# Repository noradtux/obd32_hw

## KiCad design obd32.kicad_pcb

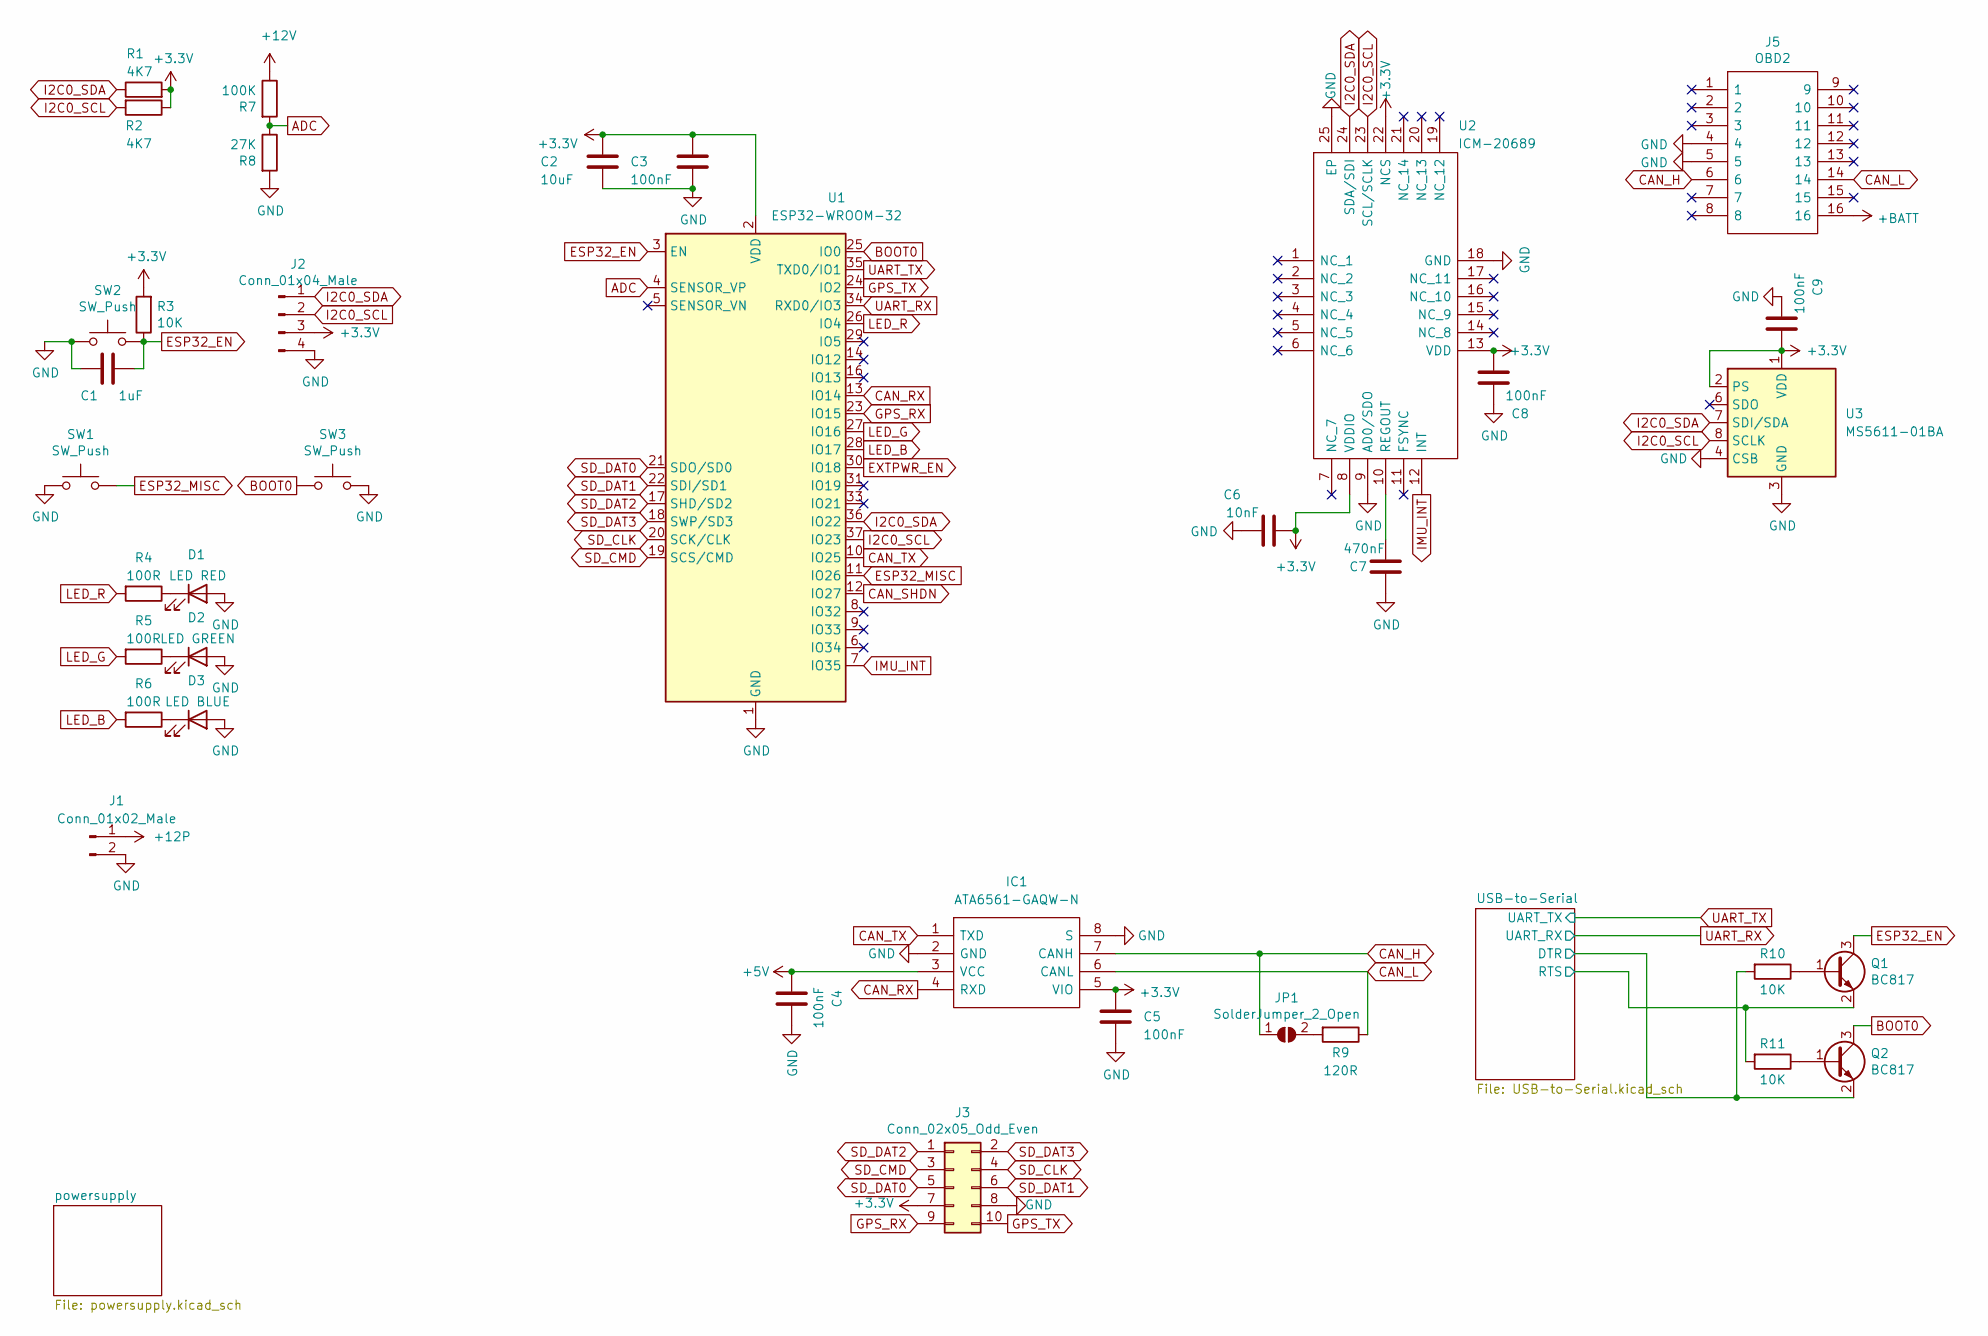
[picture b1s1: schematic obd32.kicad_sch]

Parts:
C1: 1uF; C_0603_1608Metric_Pad1.08x0.95mm_HandSolder
C2: 10uF; C_0603_1608Metric_Pad1.08x0.95mm_HandSolder
C3, C4, C5, C8, C9: 100nF; C_0603_1608Metric_Pad1.08x0.95mm_HandSolder
C6: 10nF; C_0603_1608Metric_Pad1.08x0.95mm_HandSolder
C7: 470nF; C_0603_1608Metric_Pad1.08x0.95mm_HandSolder
D1: LED RED; LED_0603_1608Metric_Pad1.05x0.95mm_HandSolder
D2: LED GREEN; LED_0603_1608Metric_Pad1.05x0.95mm_HandSolder
D3: LED BLUE; LED_0603_1608Metric_Pad1.05x0.95mm_HandSolder
IC1: ATA6561-GAQW-N; SOIC127P600X175-8N; Manufacturer_Part_Number ATA6564-GAQW1
J1: Conn_01x02_Male; Molex_Micro-Fit_3.0_43045-0200_2x01_P3.00mm_Horizontal
J2: Conn_01x04_Male; PinHeader_1x04_P2.54mm_Vertical
J3: Conn_02x05_Odd_Even; PinSocket_2x05_P2.54mm_Vertical
J5: OBD2; Manufacturer_Part_Number OBD2
JP1: SolderJumper_2_Open; SolderJumper-2_P1.3mm_Open_RoundedPad1.0x1.5mm
Q1, Q2: BC817; SOT-23
R1, R2: 4K7; R_0603_1608Metric_Pad0.98x0.95mm_HandSolder
R3, R10, R11: 10K; R_0603_1608Metric_Pad0.98x0.95mm_HandSolder
R4, R5, R6: 100R; R_0603_1608Metric_Pad0.98x0.95mm_HandSolder
R7: 100K; R_0603_1608Metric_Pad0.98x0.95mm_HandSolder
R8: 27K; R_0603_1608Metric_Pad0.98x0.95mm_HandSolder
R9: 120R; R_0603_1608Metric_Pad0.98x0.95mm_HandSolder
SW1, SW2, SW3: SW_Push; SW_SPST_B3U-3000P-B
U1: ESP32-WROOM-32
U2: ICM-20689; QFN50P400X400X95-25N-D; Manufacturer_Part_Number ICM-20689; Mouser Part Number 410-ICM-20689
U3: MS5611-01BA; LGA-8_3x5mm_P1.25mm

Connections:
+3V3: C2.1, C3.1, C5.2, C6.2, C8.2, C9.2, IC1.5 (VIO), J2.3, J3.7, R1.2, R2.1, R3.2, U1.2 (VDD), U2.8 (VDDIO), U2.13 (VDD), U2.22 (NCS), U3.1 (VDD), U3.2 (PS); also elsewhere on the board
+5V: C4.1, IC1.3 (VCC); also elsewhere on the board
+12P: J1.1; also elsewhere on the board
+12V: R7.1; also elsewhere on the board
+BATT: J5.16; also elsewhere on the board
/USB-to-Serial/DTR: Q2.2 (E), R10.2; also elsewhere on the board
/USB-to-Serial/RTS: Q1.2 (E), R11.2; also elsewhere on the board
ADC: R7.2, R8.1, U1.4 (SENSOR_VP)
BOOT0: Q2.3 (C), SW3.1, U1.25 (IO0)
CAN_H: IC1.7 (CANH), J5.6, JP1.1 (A)
CAN_L: IC1.6 (CANL), J5.14, R9.1
CAN_RX: IC1.4 (RXD), U1.13 (IO14)
CAN_SHDN: U1.12 (IO27); also elsewhere on the board
CAN_TX: IC1.1 (TXD), U1.10 (IO25)
ESP32_EN: C1.2, Q1.3 (C), R3.1, SW2.2, U1.3 (EN)
ESP32_MISC: SW1.2, U1.11 (IO26)
EXTPWR_EN: U1.30 (IO18); also elsewhere on the board
GND: C1.1, C2.2, C3.2, C4.2, C5.1, C6.1, C7.1, C8.1, C9.1, D1.2 (A), D2.2 (A), D3.2 (A), IC1.2 (GND), IC1.8 (S), J1.2, J2.4, J3.8, J5.4, J5.5, R8.2, SW1.1, SW2.1, SW3.2, U1.1 (GND), U1.15 (GND), U1.38 (GND), U1.39 (GND), U2.9 (AD0/SDO), U2.18 (GND), U2.25 (EP), U3.3 (GND), U3.4 (CSB), U3.5 (CSB); also elsewhere on the board
GPS_RX: J3.9, U1.23 (IO15)
GPS_TX: J3.10, U1.24 (IO2)
I2C0_SCL: J2.2, R2.2, U1.37 (IO23), U2.23 (SCL/SCLK), U3.8 (SCLK)
I2C0_SDA: J2.1, R1.1, U1.36 (IO22), U2.24 (SDA/SDI), U3.7 (SDI/SDA)
IMU_INT: U1.7 (IO35), U2.12 (INT)
LED_B: R6.2, U1.28 (IO17)
LED_G: R5.2, U1.27 (IO16)
LED_R: R4.2, U1.26 (IO4)
unnamed: C7.2, U2.10 (REGOUT)
unnamed: D1.1 (K), R4.1
unnamed: D2.1 (K), R5.1
unnamed: D3.1 (K), R6.1
unnamed: JP1.2 (B), R9.2
unnamed: Q1.1 (B), R10.1
unnamed: Q2.1 (B), R11.1
SD_CLK: J3.4, U1.20 (SCK/CLK)
SD_CMD: J3.3, U1.19 (SCS/CMD)
SD_DAT0: J3.5, U1.21 (SDO/SD0)
SD_DAT1: J3.6, U1.22 (SDI/SD1)
SD_DAT2: J3.1, U1.17 (SHD/SD2)
SD_DAT3: J3.2, U1.18 (SWP/SD3)
UART_RX: U1.34 (RXD0/IO3); also elsewhere on the board
UART_TX: U1.35 (TXD0/IO1); also elsewhere on the board

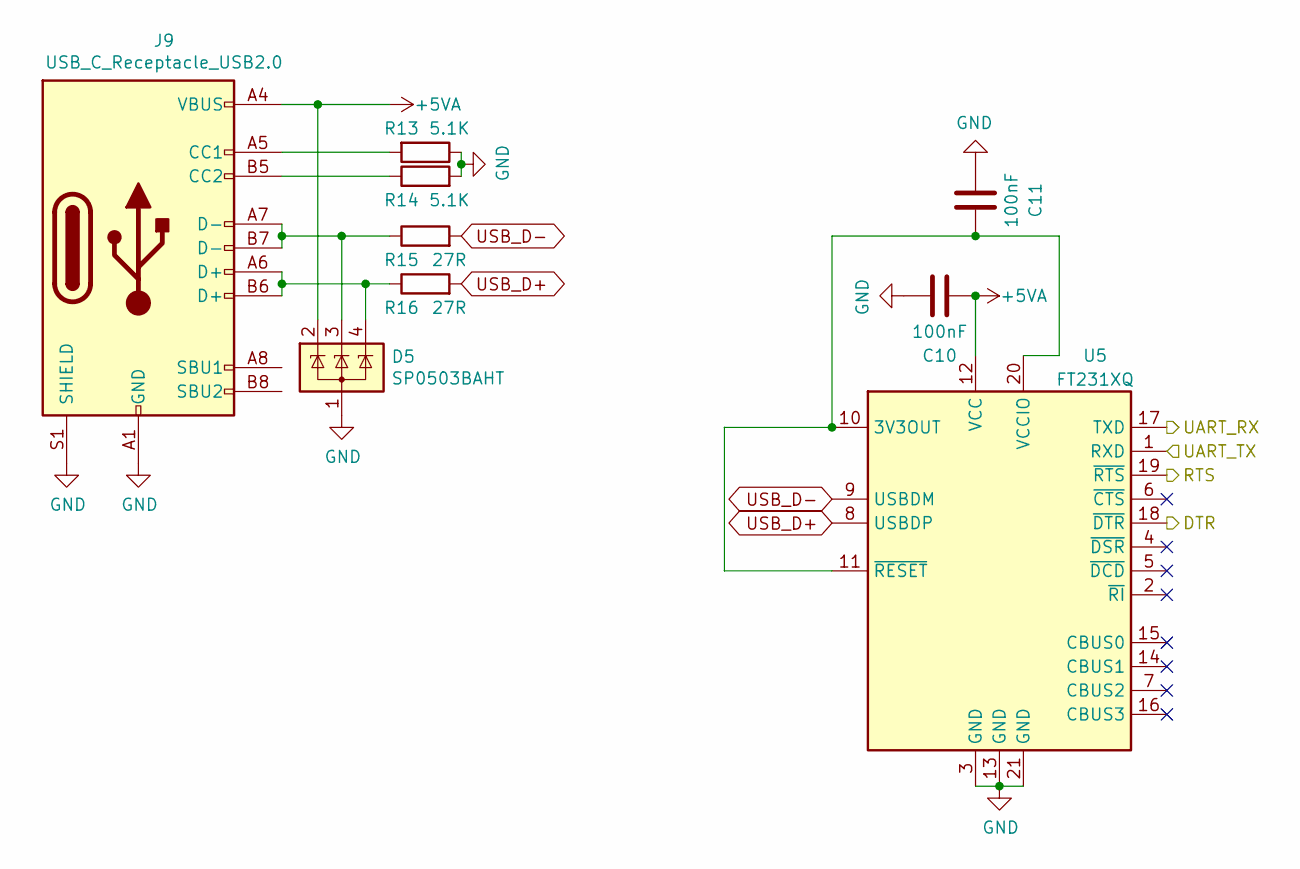
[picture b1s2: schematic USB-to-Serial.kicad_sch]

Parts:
C10, C11: 100nF; C_0603_1608Metric_Pad1.08x0.95mm_HandSolder
D5: SP0503BAHT; SOT-143
J9: USB_C_Receptacle_USB2.0; USB_C_Receptacle_JAE_DX07S016JA1
R13, R14: 5.1K; R_0603_1608Metric_Pad0.98x0.95mm_HandSolder
R15, R16: 27R; R_0603_1608Metric_Pad0.98x0.95mm_HandSolder
U5: FT231XQ; QFN-20-1EP_4x4mm_P0.5mm_EP2.5x2.5mm

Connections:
+5VA: C10.2, D5.2 (K), J9.A4 (VBUS), J9.A9 (VBUS), J9.B4 (VBUS), J9.B9 (VBUS), U5.12 (VCC); also elsewhere on the board
/USB-to-Serial/DTR: U5.18 (~DTR); also elsewhere on the board
/USB-to-Serial/RTS: U5.19 (~RTS); also elsewhere on the board
GND: C10.1, C11.2, D5.1 (A), J9.A1 (GND), J9.A12 (GND), J9.B1 (GND), J9.B12 (GND), J9.S1 (SHIELD), R13.1, R14.2, U5.3 (GND), U5.13 (GND), U5.21 (GND); also elsewhere on the board
unnamed: C11.1, U5.10 (3V3OUT), U5.11 (~RESET), U5.20 (VCCIO)
unnamed: D5.3 (K), J9.A7 (D-), J9.B7 (D-), R15.1
unnamed: D5.4 (K), J9.A6 (D+), J9.B6 (D+), R16.1
unnamed: J9.A5 (CC1), R13.2
unnamed: J9.B5 (CC2), R14.1
UART_RX: U5.17 (TXD); also elsewhere on the board
UART_TX: U5.1 (RXD); also elsewhere on the board
USB_D+: R16.2, U5.8 (USBDP)
USB_D-: R15.2, U5.9 (USBDM)

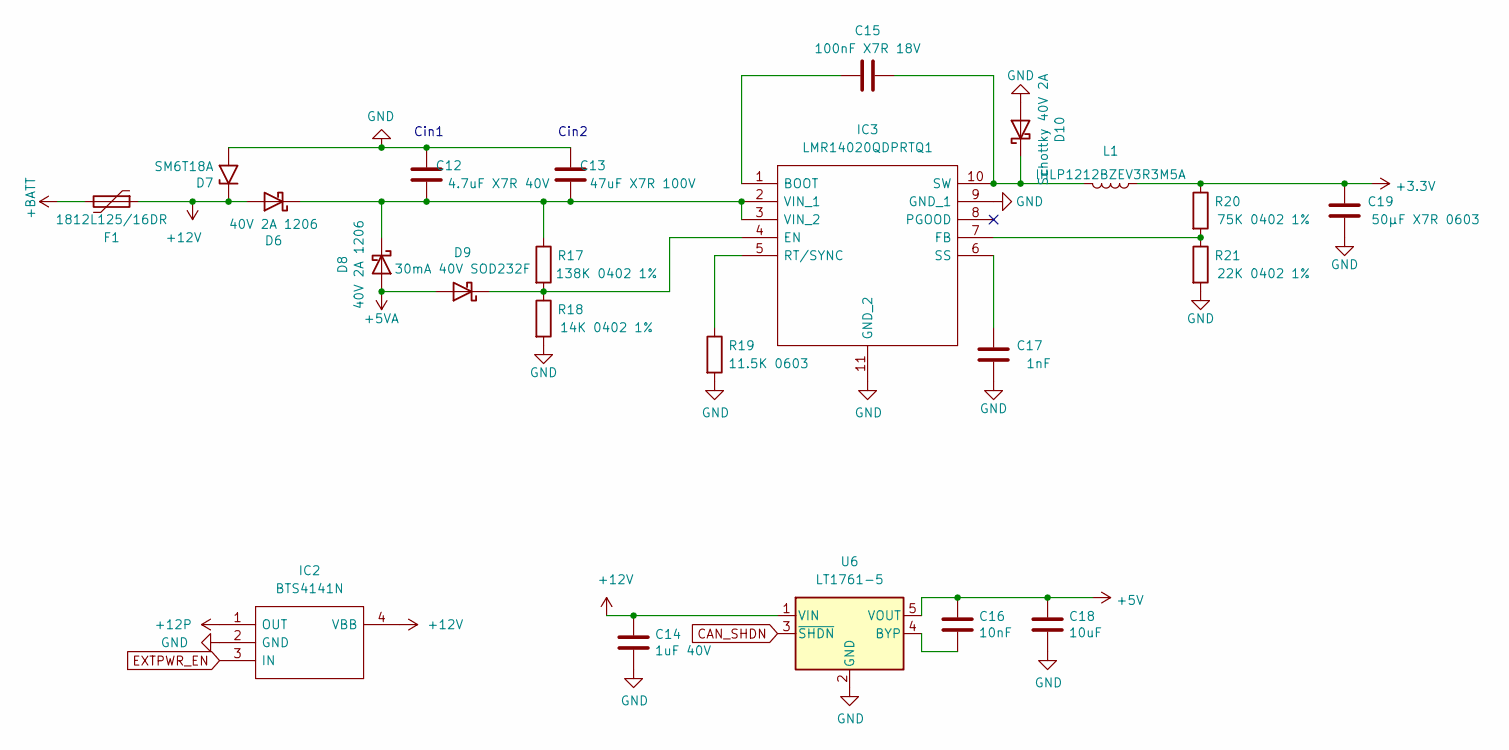
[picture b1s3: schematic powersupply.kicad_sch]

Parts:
C12: 4.7uF X7R 40V; C_0603_1608Metric_Pad1.08x0.95mm_HandSolder
C13: 47uF X7R 100V; C_0603_1608Metric_Pad1.08x0.95mm_HandSolder
C14: 1uF 40V; C_0603_1608Metric_Pad1.08x0.95mm_HandSolder
C15: 100nF X7R 18V; C_0603_1608Metric_Pad1.08x0.95mm_HandSolder
C16: 10nF; C_0603_1608Metric_Pad1.08x0.95mm_HandSolder
C17: 1nF; C_0603_1608Metric_Pad1.08x0.95mm_HandSolder
C18: 10uF; C_0603_1608Metric_Pad1.08x0.95mm_HandSolder
C19: 50µF X7R 0603; C_0603_1608Metric_Pad1.08x0.95mm_HandSolder
D6: 40V 2A 1206; D_1206_3216Metric_Castellated
D7: SM6T18A; D_SMB
D8: 40V 2A 1206; D_1206_3216Metric
D9: 30mA 40V SOD232F; D_SOD-323F
D10: Schottky 40V 2A; D_1206_3216Metric
F1: 1812L125/16DR; Fuse_1812_4532Metric_Castellated
IC2: BTS4141N; SOT-223; Manufacturer_Part_Number BTS4141N
IC3: LMR14020QDPRTQ1; SON80P400X400X80-11N; Manufacturer_Part_Number LMR14020QDPRTQ1
L1: IHLP1212BZEV3R3M5A; L_Vishay_IHLP-1212
R17: 138K 0402 1%; R_0603_1608Metric_Pad0.98x0.95mm_HandSolder
R18: 14K 0402 1%; R_0603_1608Metric_Pad0.98x0.95mm_HandSolder
R19: 11.5K 0603; R_0603_1608Metric_Pad0.98x0.95mm_HandSolder
R20: 75K 0402 1%; R_0603_1608Metric_Pad0.98x0.95mm_HandSolder
R21: 22K 0402 1%; R_0603_1608Metric_Pad0.98x0.95mm_HandSolder
U6: LT1761-5; TSOT-23-5

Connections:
+3V3: C19.2, L1.1, R20.1; also elsewhere on the board
+5V: C16.1, C18.1, U6.5 (VOUT); also elsewhere on the board
+5VA: D8.2 (A), D9.2 (A); also elsewhere on the board
+12P: IC2.1 (OUT); also elsewhere on the board
+12V: C14.1, D6.2 (A), D7.1 (A1), F1.1, IC2.4 (VBB), U6.1 (VIN); also elsewhere on the board
+BATT: F1.2; also elsewhere on the board
CAN_SHDN: U6.3 (~SHDN); also elsewhere on the board
EXTPWR_EN: IC2.3 (IN); also elsewhere on the board
GND: C12.2, C13.2, C14.2, C17.1, C18.2, C19.1, D7.2 (A2), D10.2 (A), IC2.2 (GND), IC3.9 (GND_1), IC3.11 (GND_2), R18.2, R19.2, R21.2, U6.2 (GND); also elsewhere on the board
unnamed: C12.1, C13.1, D6.1 (K), D8.1 (K), IC3.2 (VIN_1), IC3.3 (VIN_2), R17.1
unnamed: C15.1, D10.1 (K), IC3.10 (SW), L1.2
unnamed: C15.2, IC3.1 (BOOT)
unnamed: C16.2, U6.4 (BYP)
unnamed: C17.2, IC3.6 (SS)
unnamed: D9.1 (K), IC3.4 (EN), R17.2, R18.1
unnamed: IC3.5 (RT/SYNC), R19.1
unnamed: IC3.7 (FB), R20.2, R21.1

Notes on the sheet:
Cin1
Cin2

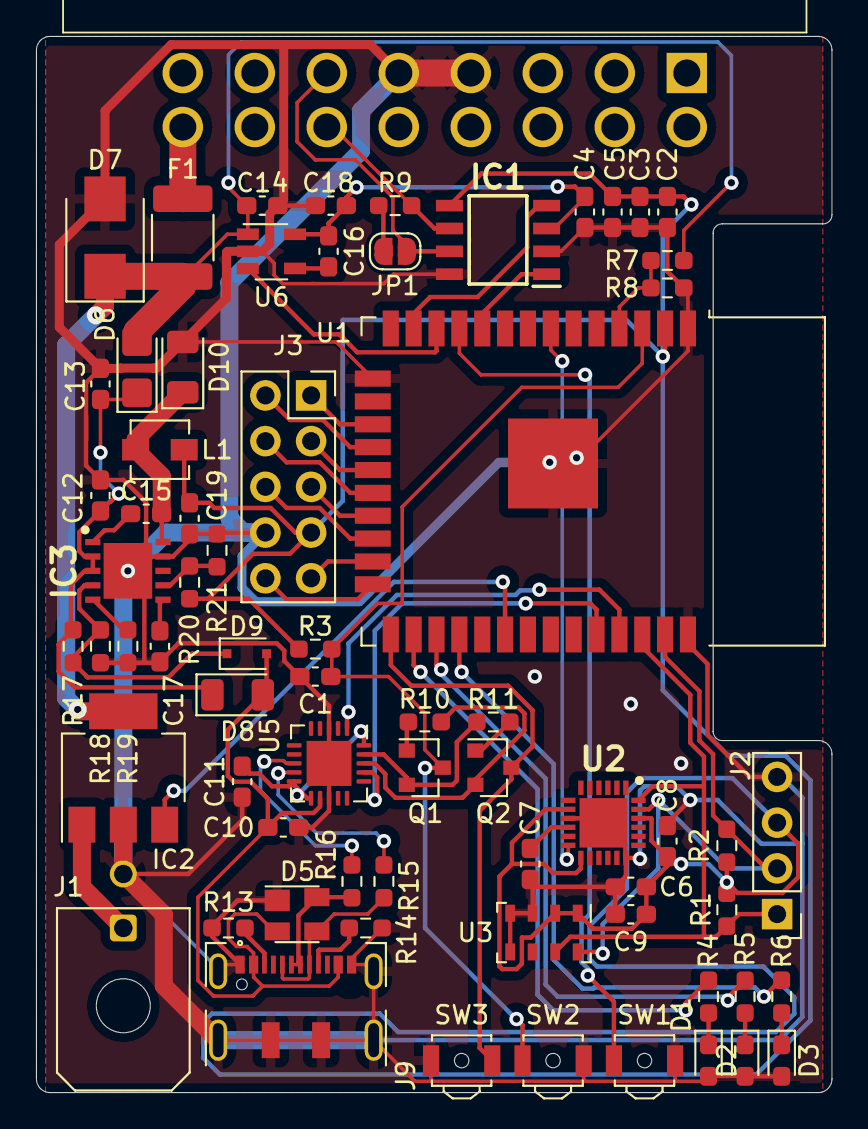
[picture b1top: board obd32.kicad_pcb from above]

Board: 2 copper layers, 44.2 x 58.7 mm, 69 parts (0 on the bottom side), 57 nets.

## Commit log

2022-01-27 fix design rule check faults
